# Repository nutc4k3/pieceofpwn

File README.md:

# pieceofpwn
Bad USB like with a touch of candy style.

**Pictures:**

**License:** CC by 4.0\
creativecommons.org/licenses/by/4.0/\
_This work is is a derivative of Digispark by Erick Kettenburg used under CC by 3.0._

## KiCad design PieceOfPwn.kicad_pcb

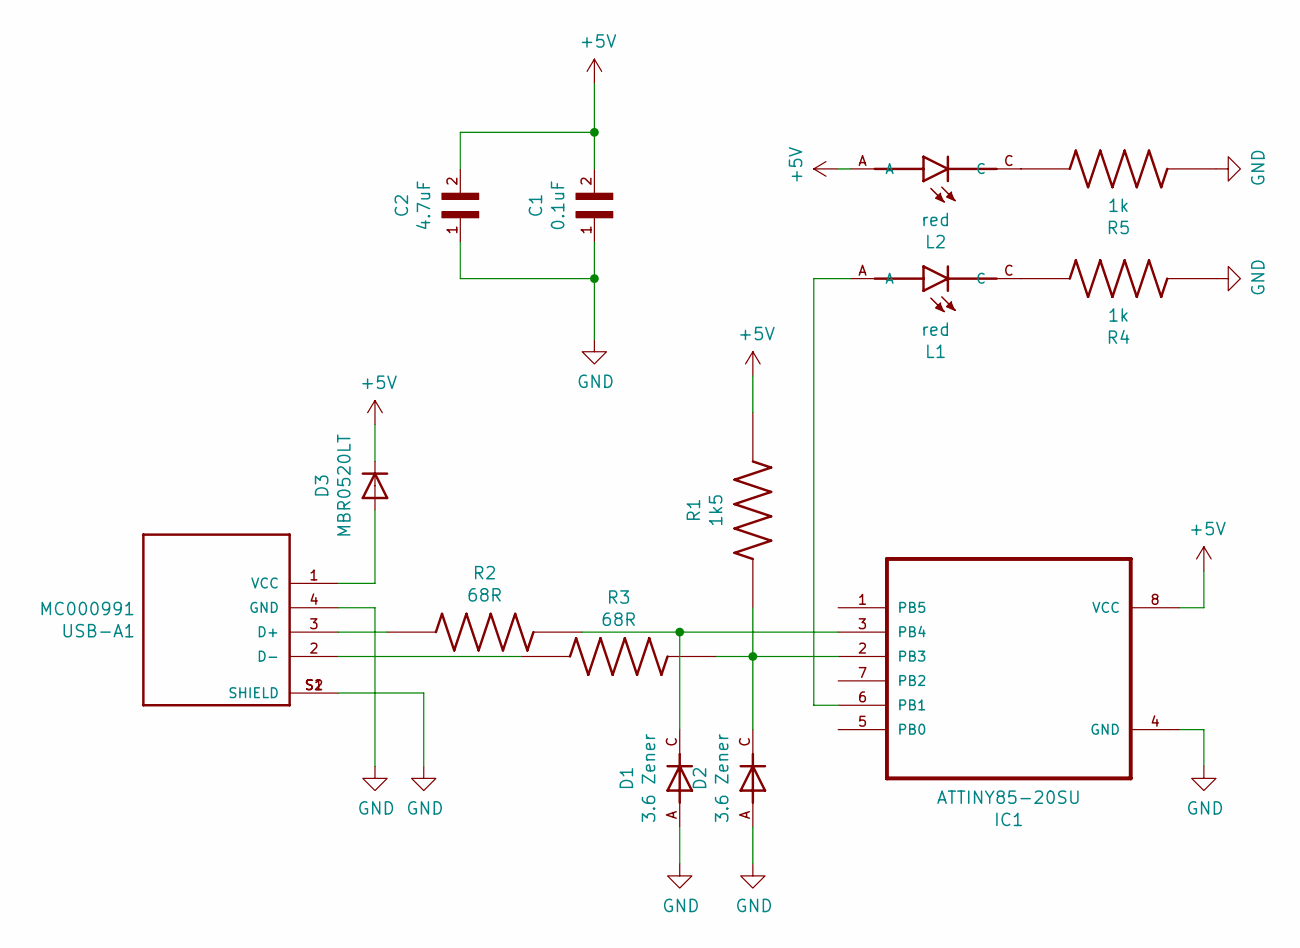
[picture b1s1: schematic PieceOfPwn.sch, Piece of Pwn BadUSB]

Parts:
C1: 0.1uF; CAPC1608X90N
C2: 4.7uF; CAPC2012X140N
D1, D2: 3.6 Zener; SODFL2512X90N
D3: MBR0520LT; SOD123
IC1: ATTINY85-20SU; SOIC127P798X216-8N
L1, L2: red; LEDM1608X80
R1: 1k5; RESC2012X65N
R2, R3: 68R; RESC2012X50N
R4, R5: 1k; RESC1608X59N
USB-A1: MC000991; MULTICOMP_MC000991

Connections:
+5V: C1.2, C2.2, D3.C, IC1.8 (VCC), L2.A, R1.2
GND: C1.1, C2.1, D1.A, D2.A, IC1.4 (GND), R4.1, R5.1, USB-A1.4 (GND), USB-A1.S1 (SHIELD), USB-A1.S2 (SHIELD)
unnamed: D1.C, IC1.3 (PB4), R2.2
unnamed: D2.C, IC1.2 (PB3), R1.1, R3.2
unnamed: D3.A, USB-A1.1 (VCC)
unnamed: IC1.6 (PB1), L1.A
unnamed: L1.C, R4.2
unnamed: L2.C, R5.2
unnamed: R2.1, USB-A1.3 (D+)
unnamed: R3.1, USB-A1.2 (D-)

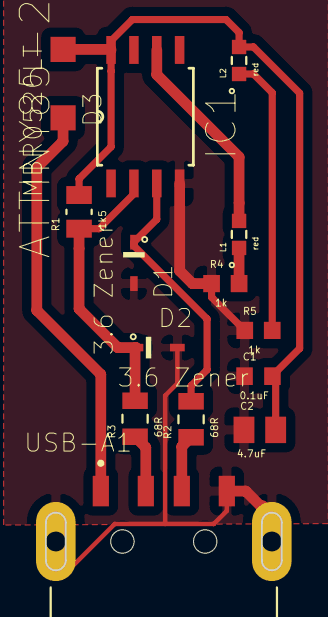
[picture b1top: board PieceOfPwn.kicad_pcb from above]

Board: 2 copper layers, 14 parts (0 on the bottom side), 10 nets.

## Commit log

2020-01-17 Set theme jekyll-theme-hacker
2020-01-17 Create CNAME
2020-04-14 added imgs
